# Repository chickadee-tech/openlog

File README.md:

# Chickadee Tech OpenLog Cradle Polystack Mod #
This mod cradles an OpenLog to connect it to the control board. It is not in active production because its total cost is greater than the native microSD mod.

## Documentation ##
See the [wiki](https://github.com/chickadee-tech/openlog/wiki) for documentation.

## Polystack ##
This **mod** board is part of the Polystack platform for modular microcontrol systems. More information on the platform can be found at [polystack.org](http://polystack.org).

## Support ##
If you need support with a board you own or have development questions please email support@chickadee.tech or check [chickadee.tech/support](https://chickadee.tech/support) for other ways to get support.

## Contributing ##
Please note that this project is released with a [Contributor Code of Conduct](CODE_OF_CONDUCT.md). By participating in this project you agree to abide by its terms.

### Setup ###
Components and footprints for PCB parts are not included in this repository. Instead, checkout the [chickadee-tech/kicad-libs](https://github.com/chickadee-tech/kicad-libs) repository in the same directory that this repository is checked out in. All part definitions should be relative so that they will load correctly.

### Pull requests ###
For fixes please submit a pull request to the original repository. After the pull request is merged, check the [Chickadee Tech Active Contributor Discount (ACD)](https://chickadee.tech/active-contributor) to see if you are eligible for a discount code to use on your next purchase.

### Derivatives ###
If developing your own version of the openlog board please remove all Chickadee Tech trademarks and follow the [CC-BY license](LICENSE). While not required, please consider open sourcing your modifications so others can learn from your improvements. If you do, then email support@chickadee.tech and we may choose to add your project to the ACD.

You may also license the Polystack logo for free by emailing support@chickadee.tech. We'll ask for your gerbers to ensure the design complies with specifications laid out [here](https://github.com/chickadee-tech/polystack/wiki) and provide written permission to use the trademark after compliance has been demonstrated.

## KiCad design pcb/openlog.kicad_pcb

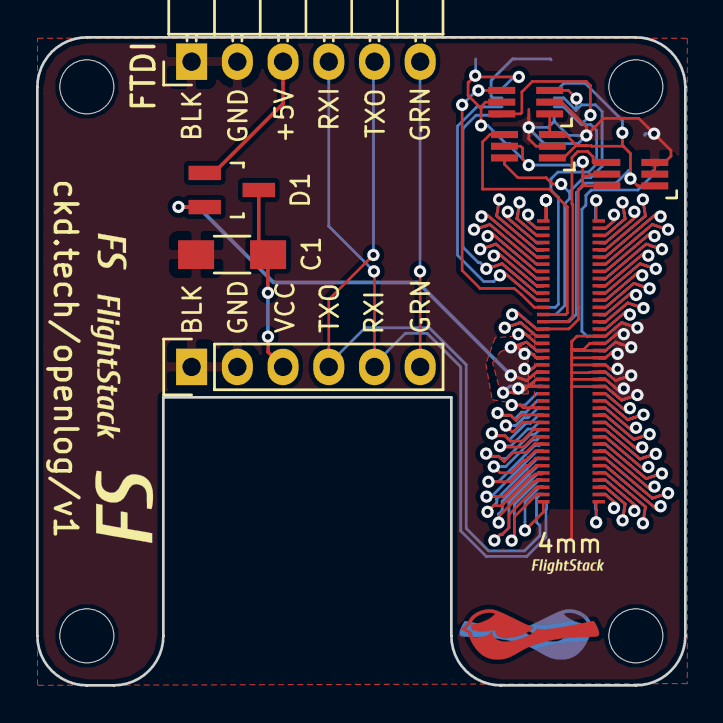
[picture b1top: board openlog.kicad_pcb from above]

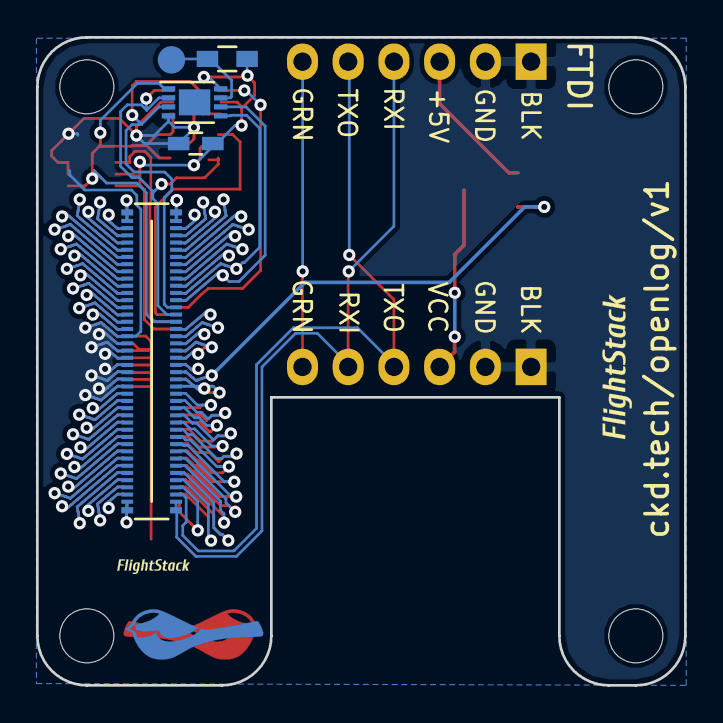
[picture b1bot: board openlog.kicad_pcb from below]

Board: 2 copper layers, 36.0 x 36.0 mm, 13 parts (5 on the bottom side), 75 nets.

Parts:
C1: 10uF; C_1206_HandSoldering
CRADLE_PORT1: CONN_01X06; Pin_Header_Straight_1x06
D1: D_Schottky_x2_KCom_AAK; SOT-23_Handsoldering
PORT_ANDOR1: SN74LVC1G0832; SC-70-6_Handsoldering
PORT_C1: 0.1uF; C_0603_HandSoldering
PORT_IC1: AT24CS02-MAHM; DFN-8-1EP_3x2mm_Pitch0.5mm
PORT_IN1: CKD_SANDWICH; DF40-80pin-Header
PORT_INV1: SN74LVC1G58; SC-70-6_Handsoldering
PORT_OUT1: CKD_SANDWICH; DF40-3-4mm-80pin-Receptacle
PORT_P1: CONN_01X01; Measurement_Point_Round-SMD-Pad_Small
PORT_R1: 10k; R_0603_HandSoldering
PORT_XOR1: SN74LVC1G58; SC-70-6_Handsoldering
PROGRAM_PORT1: CONN_01X06; Pin_Header_Angled_1x06

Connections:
+5V: D1.2, PORT_IN1.19, PORT_IN1.20, PORT_IN1.21, PORT_IN1.22, PORT_IN1.23, PORT_IN1.24, PORT_OUT1.19, PORT_OUT1.20, PORT_OUT1.21, PORT_OUT1.22, PORT_OUT1.23, PORT_OUT1.24
/ExpansionPort/3V3_0.3A_E: PORT_IN1.17, PORT_OUT1.17
/ExpansionPort/3V3_0.3A_LL: PORT_ANDOR1.5, PORT_C1.1, PORT_IC1.8, PORT_IN1.16, PORT_INV1.5, PORT_INV1.6, PORT_OUT1.16, PORT_R1.2, PORT_XOR1.5
/ExpansionPort/+BATT: PORT_IN1.18, PORT_OUT1.18
/ExpansionPort/ADC1: PORT_IN1.49, PORT_OUT1.49
/ExpansionPort/ADC2: PORT_IN1.50, PORT_OUT1.50
/ExpansionPort/BOOT: PORT_IN1.65, PORT_OUT1.65
/ExpansionPort/CAN_HI: PORT_IN1.67, PORT_OUT1.67
/ExpansionPort/CAN_LO: PORT_IN1.68, PORT_OUT1.68
/ExpansionPort/GPIO1: PORT_IN1.5, PORT_OUT1.5
/ExpansionPort/GPIO2: PORT_IN1.6, PORT_OUT1.6
/ExpansionPort/GPIO3: PORT_IN1.7, PORT_OUT1.7
/ExpansionPort/GPIO4: PORT_IN1.8, PORT_OUT1.8
/ExpansionPort/GPIO5: PORT_IN1.9, PORT_OUT1.9
/ExpansionPort/GPIO6: PORT_IN1.10, PORT_OUT1.10
/ExpansionPort/HEIGHT_1: PORT_ANDOR1.1, PORT_IC1.1, PORT_IN1.15, PORT_INV1.1, PORT_XOR1.1, PORT_XOR1.3
/ExpansionPort/HEIGHT_2: PORT_ANDOR1.3, PORT_IC1.2, PORT_IN1.14, PORT_XOR1.6
/ExpansionPort/HEIGHT_4: PORT_ANDOR1.6, PORT_IC1.3, PORT_IN1.13
/ExpansionPort/NEW_HEIGHT_1: PORT_INV1.4, PORT_OUT1.15
/ExpansionPort/NEW_HEIGHT_2: PORT_OUT1.14, PORT_XOR1.4
/ExpansionPort/NEW_HEIGHT_4: PORT_ANDOR1.4, PORT_OUT1.13
/ExpansionPort/RESET: PORT_IN1.66, PORT_OUT1.66
/ExpansionPort/SDMMC1_CK: PORT_IN1.55, PORT_OUT1.55
/ExpansionPort/SDMMC1_CMD: PORT_IN1.56, PORT_OUT1.56
/ExpansionPort/SDMMC1_D0: PORT_IN1.51, PORT_OUT1.51
/ExpansionPort/SDMMC1_D1: PORT_IN1.52, PORT_OUT1.52
/ExpansionPort/SDMMC1_D2: PORT_IN1.53, PORT_OUT1.53
/ExpansionPort/SDMMC1_D3: PORT_IN1.54, PORT_OUT1.54
/ExpansionPort/SPI1_MISO: PORT_IN1.79, PORT_OUT1.79
/ExpansionPort/SPI1_MOSI: PORT_IN1.80, PORT_OUT1.80
/ExpansionPort/SPI1_NSS: PORT_IN1.77, PORT_OUT1.77
/ExpansionPort/SPI1_SCK: PORT_IN1.78, PORT_OUT1.78
/ExpansionPort/SPI2_MISO: PORT_IN1.75, PORT_OUT1.75
/ExpansionPort/SPI2_MOSI: PORT_IN1.76, PORT_OUT1.76
/ExpansionPort/SPI2_NSS: PORT_IN1.73, PORT_OUT1.73
/ExpansionPort/SPI2_SCK: PORT_IN1.74, PORT_OUT1.74
/ExpansionPort/SPI3_MISO: PORT_IN1.71, PORT_OUT1.71
/ExpansionPort/SPI3_MOSI: PORT_IN1.72, PORT_OUT1.72
/ExpansionPort/SPI3_NSS: PORT_IN1.69, PORT_OUT1.69
/ExpansionPort/SPI3_SCK: PORT_IN1.70, PORT_OUT1.70
/ExpansionPort/TIM1: PORT_IN1.1, PORT_OUT1.1
/ExpansionPort/TIM2: PORT_IN1.2, PORT_OUT1.2
/ExpansionPort/TIM3: PORT_IN1.3, PORT_OUT1.3
/ExpansionPort/TIM4: PORT_IN1.4, PORT_OUT1.4
/ExpansionPort/TIMG1_CH1: PORT_IN1.41, PORT_OUT1.41
/ExpansionPort/TIMG1_CH2: PORT_IN1.42, PORT_OUT1.42
/ExpansionPort/TIMG1_CH3: PORT_IN1.43, PORT_OUT1.43
/ExpansionPort/TIMG1_CH4: PORT_IN1.44, PORT_OUT1.44
/ExpansionPort/TIMG2_CH1: PORT_IN1.45, PORT_OUT1.45
/ExpansionPort/TIMG2_CH2: PORT_IN1.46, PORT_OUT1.46
/ExpansionPort/TIMG2_CH3: PORT_IN1.47, PORT_OUT1.47
/ExpansionPort/TIMG2_CH4: PORT_IN1.48, PORT_OUT1.48
/ExpansionPort/UART1_RX: CRADLE_PORT1.5, PORT_IN1.40, PROGRAM_PORT1.4
/ExpansionPort/UART1_TX: CRADLE_PORT1.4, PORT_IN1.39, PROGRAM_PORT1.5
/ExpansionPort/UART2_RX: PORT_IN1.38, PORT_OUT1.40
/ExpansionPort/UART2_TX: PORT_IN1.37, PORT_OUT1.39
/ExpansionPort/UART3_RX: PORT_IN1.36, PORT_OUT1.38
/ExpansionPort/UART3_TX: PORT_IN1.35, PORT_OUT1.37
/ExpansionPort/UART4_RX: PORT_IN1.34, PORT_OUT1.36
/ExpansionPort/UART4_TX: PORT_IN1.33, PORT_OUT1.35
/ExpansionPort/UART5_RX: PORT_IN1.32, PORT_OUT1.34
/ExpansionPort/UART5_TX: PORT_IN1.31, PORT_OUT1.33
/ExpansionPort/UART6_RX: PORT_IN1.30, PORT_OUT1.32
/ExpansionPort/UART6_TX: PORT_IN1.29, PORT_OUT1.31
/ExpansionPort/UART7_RX: PORT_IN1.28, PORT_OUT1.30
/ExpansionPort/UART7_TX: PORT_IN1.27, PORT_OUT1.29
/ExpansionPort/UART8_RX: PORT_IN1.26, PORT_OUT1.28
/ExpansionPort/UART8_TX: PORT_IN1.25, PORT_OUT1.27
/ExpansionPort/i2c_SCL: PORT_IC1.6, PORT_IN1.12, PORT_OUT1.12
/ExpansionPort/i2c_SDA: PORT_IC1.5, PORT_IN1.11, PORT_OUT1.11
/FTDI_PWR: D1.1, PROGRAM_PORT1.3
GNDPWR: C1.2, CRADLE_PORT1.1, CRADLE_PORT1.2, PORT_ANDOR1.2, PORT_C1.2, PORT_IC1.4, PORT_IN1.57, PORT_IN1.58, PORT_IN1.59, PORT_IN1.60, PORT_IN1.61, PORT_IN1.62, PORT_IN1.63, PORT_IN1.64, PORT_INV1.2, PORT_INV1.3, PORT_OUT1.57, PORT_OUT1.58, PORT_OUT1.59, PORT_OUT1.60, PORT_OUT1.61, PORT_OUT1.62, PORT_OUT1.63, PORT_OUT1.64, PORT_XOR1.2, PROGRAM_PORT1.1, PROGRAM_PORT1.2
unnamed: C1.1, CRADLE_PORT1.3, D1.3
unnamed: CRADLE_PORT1.6, PROGRAM_PORT1.6
unnamed: PORT_IC1.7, PORT_P1.1, PORT_R1.1

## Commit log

2016-01-26 OpenLog cradle v1.
2016-07-07 Add license information to many files. PCB design files are CC-BY and code is MIT license.
2016-07-07 Convert to relative component and footprint paths.
